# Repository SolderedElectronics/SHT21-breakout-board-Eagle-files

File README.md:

# SHT21 temperature & humidity sensor breakout Eagle files
## Image

[SHT21 breakout(101378)][board]

## Description and details
SHT21 became icon of industrial temperature & humidity sensor. Device provides calibratied, linearized signal in digital I2C format. Sensor is made in Switzerland and offers great preformances with proven stability and durability. 

## Repository content
This repo contains Cadsoft Eagle .sch and .brd files for BTR board. It also contains schematic in .pdf created from .sch Eagle file. 
Files have been arranged into folders for navigating between different versions of board. 
Tip: layer 200 shows top silkscreen and layer 208 should be bottom silkscreen. tParts and bParts are not used.

## Docs
- [SHT21 breakout product page][board]
- [SHT21 Arduino library][library]

## Board versions
- v1.0 - inital version

## License info
This product is open-source. Yay!
For any tech questions, contact us at techsupport@e-radionica.com
If you find an Issue, please open one at GitHub. If you can improve our product, fork it!

e-r.io Team.

[board]: https://e-radionica.com/en/sht21-humidity-and-temperature-sensor.html
[library]: https://github.com/e-radionicacom/SHT21-Arduino-Library

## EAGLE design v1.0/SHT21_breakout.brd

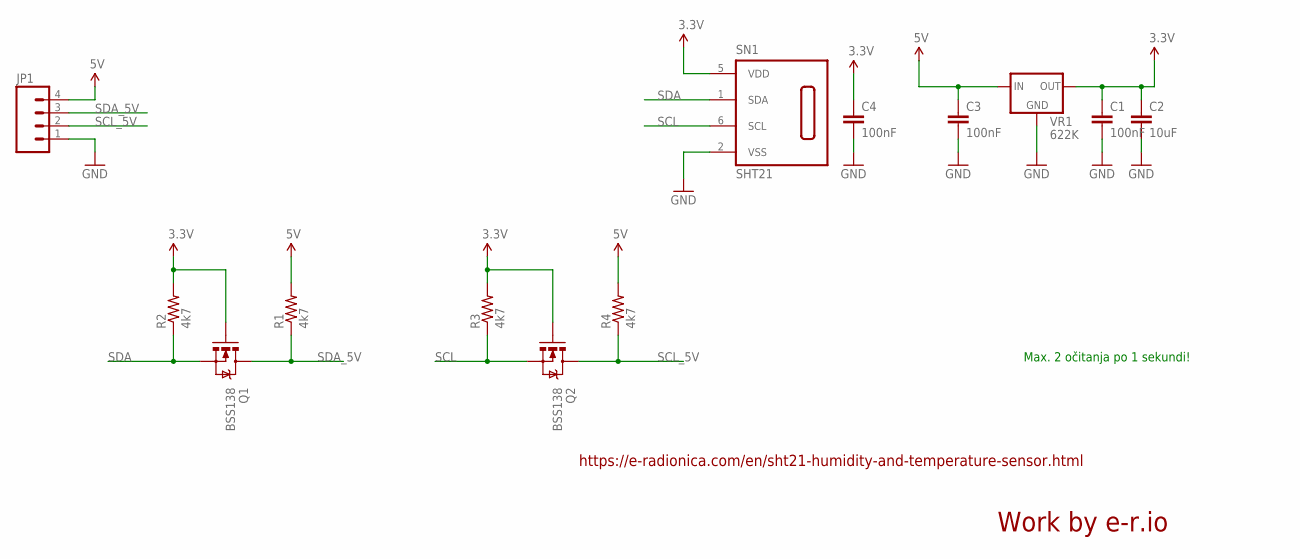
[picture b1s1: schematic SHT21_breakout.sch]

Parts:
C1, C3, C4: 100nF; 0603-CAP
C2: 10uF; 1206
JP1: M04PTH; 1X04
Q1, Q2: BSS138; SOT23-3
R1, R2, R3, R4: 4k7; 0603-RES
SN1: SHT21; DFN6/SHT
VR1: 622K; 662K

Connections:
3.3V: C1.1, C2.1, C4.1, Q1.1 (G), Q2.1 (G), R2.2, R3.2, SN1.5 (VDD), VR1.OUT
5V: C3.1, JP1.4, R1.2, R4.2, VR1.IN
GND: C1.2, C2.2, C3.2, C4.2, JP1.1, SN1.2 (VSS), VR1.GND
SCL: Q2.2 (S), R3.1, SN1.6 (SCL)
SCL_5V: JP1.2, Q2.3 (D), R4.1
SDA: Q1.2 (S), R2.1, SN1.1 (SDA)
SDA_5V: JP1.3, Q1.3 (D), R1.1

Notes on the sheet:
Max. 2 očitanja po 1 sekundi!
https://e-radionica.com/en/sht21-humidity-and-temperature-sensor.html
Work by e-r.io

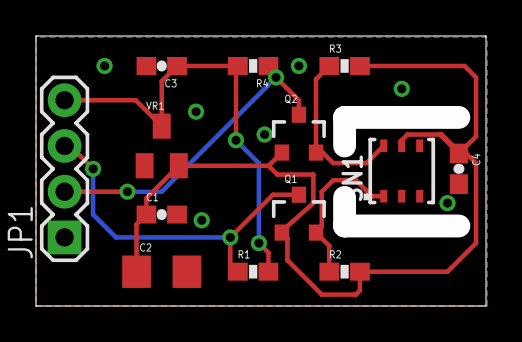
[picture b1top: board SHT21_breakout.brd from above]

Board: 2 copper layers, 23.7 x 13.7 mm, 17 parts (0 on the bottom side), 7 nets.

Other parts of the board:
U$1: LUDI_LOGO_BACK
U$6: NOVI_LOGO-4MM
U$7: OSH3MM
U$8: E-RADIONICA.COM_MADE_IN_BACK!

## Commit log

2017-06-06 Init

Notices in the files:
parts and their libraries:
SparkFun: Licensing: CC v3.0 Share-Alike You are welcome to use this library for commercial purposes.
sensirion: Copyright (C) 2011, Bob Starr
